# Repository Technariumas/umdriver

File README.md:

# umdriver
Universal AC motor driver

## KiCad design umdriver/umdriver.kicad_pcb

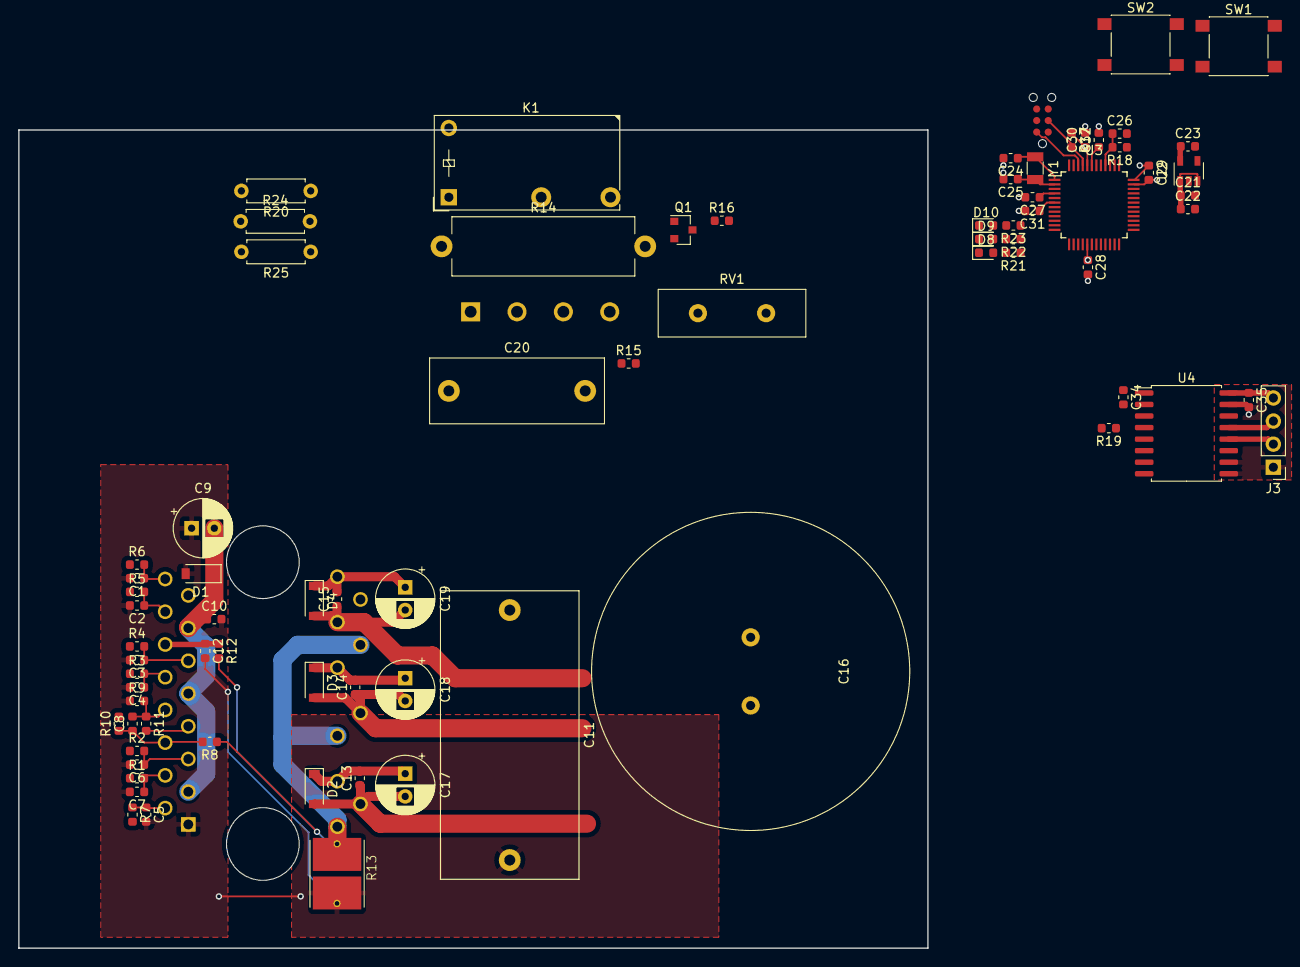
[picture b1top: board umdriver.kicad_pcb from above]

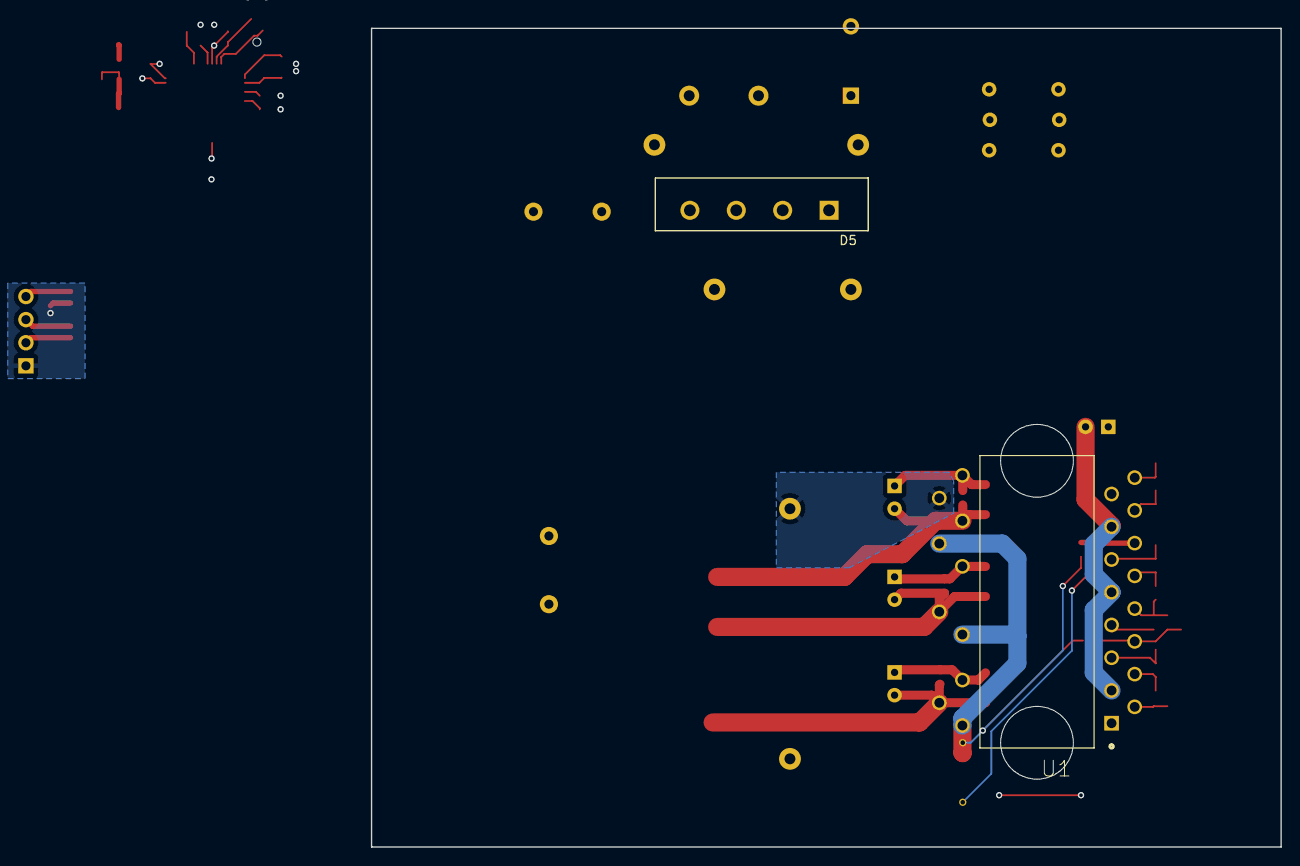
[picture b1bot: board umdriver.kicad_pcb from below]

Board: 2 copper layers, 100.0 x 90.0 mm, 79 parts (2 on the bottom side), 51 nets.

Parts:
C1, C2, C3, C4, C5, C6, C7, C12: 1n; C_0603_1608Metric
C8: 100p; C_0603_1608Metric
C9, C17, C18, C19: 10u; CP_Radial_D6.3mm_P2.50mm
C10: 0.1u; C_0603_1608Metric
C11: 7u 650V; C_Rect_L31.5mm_W15.0mm_P27.50mm_MKS4
C13, C14, C15: 2.2u; C_0603_1608Metric
C16: >9000; C_Radial_D18.0mm_H35.5mm_P7.50mm
C20: C; C_Rect_L19.0mm_W7.0mm_P15.00mm_MKS4
C21, C22, C23: 4.7u; C_0603_1608Metric
C24, C25: 22p; C_0603_1608Metric
C26, C27, C28, C29, C30, C31, C32, C34, C35: 1u; C_0603_1608Metric
D1, D2, D3, D4: 20V; D_SOD-123
D5: D_Bridge_+AA-; Diode_Bridge_18.5x5.5
D8, D9, D10: LED; LED_0603_1608Metric
J1: SWD; TC2030-MCP-NL
J3: Isolated rs485; Pin_Header_Straight_1x04_Pitch2.54mm
K1: FINDER-32.21-x000; Relay_SPST_Finder_32.21-x300
Q1: Q_NMOS_GDS; SOT-23
R1, R2, R3, R4, R5, R6: 100; R_0603_1608Metric
R7, R12, R17, R18, R21, R22, R23: 1k; R_0603_1608Metric
R8, R9: 1.0k; R_0603_1608Metric
R10, R11: 1.9k; R_0603_1608Metric
R13: 0.090 7W; RESC_WSHM2818R0150FEA
R14: R; R_Axial_Power_L20.0mm_W6.4mm_P22.40mm
R15, R16: R; R_0603_1608Metric
R19: 1M; R_0603_1608Metric
R20, R24, R25: R; R_Axial_DIN0207_L6.3mm_D2.5mm_P7.62mm_Horizontal
RV1: Varistor; C_Disc_D16.0mm_W5.0mm_P7.50mm
SW1: SW_Reset; SW_Push_1P1T_NO_6x6mm_H9.5mm
SW2: SW_Test; SW_Push_1P1T_NO_6x6mm_H9.5mm
U1: STGIPQ8C60T; ST_STGIPQ8C60T-HZ
U2: NCP718; SOT-23-5
U3: ATSAMD21G18A-AUT; TQFP-48_7x7mm_P0.5mm
U4: ISO3088DW; SOIC-16W_7.5x10.3mm_P1.27mm
Y1: 32.768; Crystal_SMD_3215-2pin_3.2x1.5mm

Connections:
+3V3: C23.1, C28.1, C29.1, C30.1, C31.1, C34.1, R7.2, R17.1, R18.1, U2.5, U3.6, U3.17, U3.36, U3.44, U4.1
+15V: C9.2, C10.1, C21.1, C22.1, D1.1, K1.A2, U1.3, U1.9, U1.13, U2.1, U2.3
/HINUF: C2.1, R5.2, U1.14
/HINVF: C4.1, R3.2, U1.10
/HINWF: C7.1, R1.2, U1.4
/ISENSE: R11.2, U1.7
/LINUF: C1.1, R6.2, U1.16
/LINVF: C3.1, R4.2, U1.11
/LINWF: C6.1, R2.2, U1.5
/Microcontroller/ISO_A: J3.2, U4.12
/Microcontroller/ISO_B: J3.3, U4.13
/Microcontroller/ISO_GND: C35.2, J3.1, U4.9, U4.10, U4.15
/Microcontroller/ISO_VCC: C35.1, J3.4, U4.16
/Microcontroller/LED1: R21.1, U3.9
/Microcontroller/LED2: R22.1, U3.10
/Microcontroller/LED3: R23.1, U3.8
/Microcontroller/MCU_AREF: C27.1, U3.4
/Microcontroller/RX: U3.38, U4.3
/Microcontroller/SWD_CLK: J1.3, R17.2, U3.45
/Microcontroller/SWD_IO: J1.2, U3.46
/Microcontroller/TX: U3.37, U4.6
/Microcontroller/~MCU_RST: C26.1, R18.2, SW1.2, U3.40
/Microcontroller/~RS485_RE: R19.1, U3.15, U4.4, U4.5
/NTC: C5.1, R7.1, U1.2
/Power Input/DC_BUS_MON: R24.2, R25.1
/Power Input/INRUSH_BYPASS: R15.2, R16.1
/Power Input/LINE_L: C20.1, K1.11, R14.1, RV1.1
/Power Input/LINE_N: C20.2, D5.3, RV1.2
/UOUT: C15.1, C19.2, D4.2, U1.19
/VBOOTU: C15.2, C19.1, D4.1, U1.17
/VBOOTV: C14.2, C18.1, D3.1, U1.21
/VBOOTW: C13.2, C17.1, D2.1, U1.24
/VOUT: C14.1, C18.2, D3.2, U1.22
/VSHUNT: R8.1, R12.2, R13.1, U1.20, U1.23, U1.26
/WOUT: C13.1, C17.2, D2.2, U1.25
GND: C1.2, C2.2, C3.2, C4.2, C5.2, C6.2, C7.2, C9.1, C10.2, C11.2, C12.2, C16.2, C21.2, C22.2, C23.2, C24.2, C25.2, C26.2, C27.2, C28.2, C29.2, C30.2, C31.2, C32.2, C34.2, D1.2, D5.4, D8.1, D9.1, D10.1, J1.6, Q1.3, R9.1, R13.2, R16.2, R19.2, R25.2, SW1.1, SW2.1, U1.1, U2.2, U3.5, U3.18, U3.35, U3.42, U4.2, U4.7, U4.8
unnamed: C8.1, R8.2, R10.1, U1.6
unnamed: C8.2, R9.2, R11.1, U1.8
unnamed: C12.1, R12.1, U1.12
unnamed: C24.1, U3.1, Y1.2
unnamed: C25.1, U3.2, Y1.1
unnamed: C32.1, U3.43
unnamed: D5.2, K1.14, R14.2
unnamed: D8.2, R21.2
unnamed: D9.2, R22.2
unnamed: D10.2, R23.2
unnamed: K1.A1, Q1.2
unnamed: Q1.1, R15.1
unnamed: R20.2, R24.1
unnamed: SW2.2, U3.7
VBUS: C11.1, C16.1, D5.1, R20.1, U1.18

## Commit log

2020-02-11 Initial. Motor driver section somewhat done. Copy pasted MCU section.
2020-02-11 cleanup
2020-02-12 Add and fix some 3d models
2020-02-12 Add battery monitoring, connect mcu lines to outside
2020-02-12 Update issue templates
